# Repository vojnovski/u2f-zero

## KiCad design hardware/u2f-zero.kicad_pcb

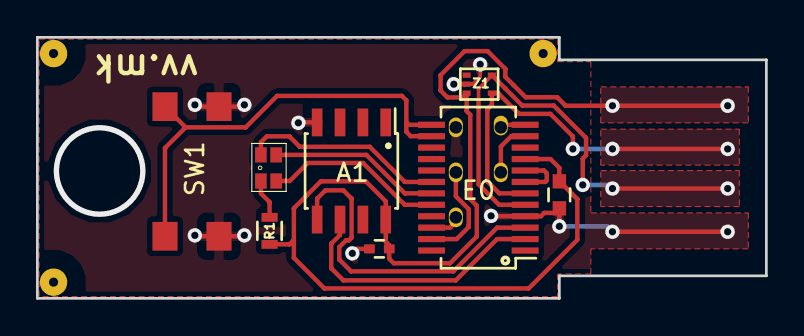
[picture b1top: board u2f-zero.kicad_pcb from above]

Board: 2 copper layers, 40.5 x 14.5 mm, 16 parts (0 on the bottom side), 16 nets.

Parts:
A1: ATECC508A; SOIC-8_3.9x4.9mm_Pitch1.27mm
C2CK1, C2D1: debug-pin; debug
C3: 0.1uF; C_0402
C4: 4.7uF; C_0603
E0: EFM8UB1_24pin; QSOP-24_3.9x8.7mm_Pitch0.635mm_fat
F1, F2, F3: u2f-fiducial
GND1: debug-pin; debug
R1: 100; R_0603
RGB1: CA_RGB; LED-0606
RX1: debug-pin; debug
SW1: SW_PUSH; u2f-button
TX1: debug-pin; debug
Z1: DF5A5.6JE; SOT-553

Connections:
/+5V: A1.8, C3.1, C4.2, E0.9, R1.1, Z1.3
/C2CK: C2CK1.1, E0.11
/C2D: C2D1.1, E0.12
/HD+: E0.5, Z1.5
/HD-: E0.6, Z1.4
/RX: E0.22, RX1.1
/TX: E0.23, TX1.1
GND: A1.4, C3.2, C4.1, E0.4, GND1.1, SW1.2, Z1.2
unnamed: A1.5, E0.3
unnamed: A1.6, E0.2
unnamed: E0.7, E0.8
unnamed: E0.13, E0.14, SW1.1
unnamed: E0.18, RGB1.1
unnamed: E0.19, RGB1.2
unnamed: E0.20, RGB1.3
unnamed: R1.2, RGB1.4

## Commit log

2018-01-16 Change PCB text
